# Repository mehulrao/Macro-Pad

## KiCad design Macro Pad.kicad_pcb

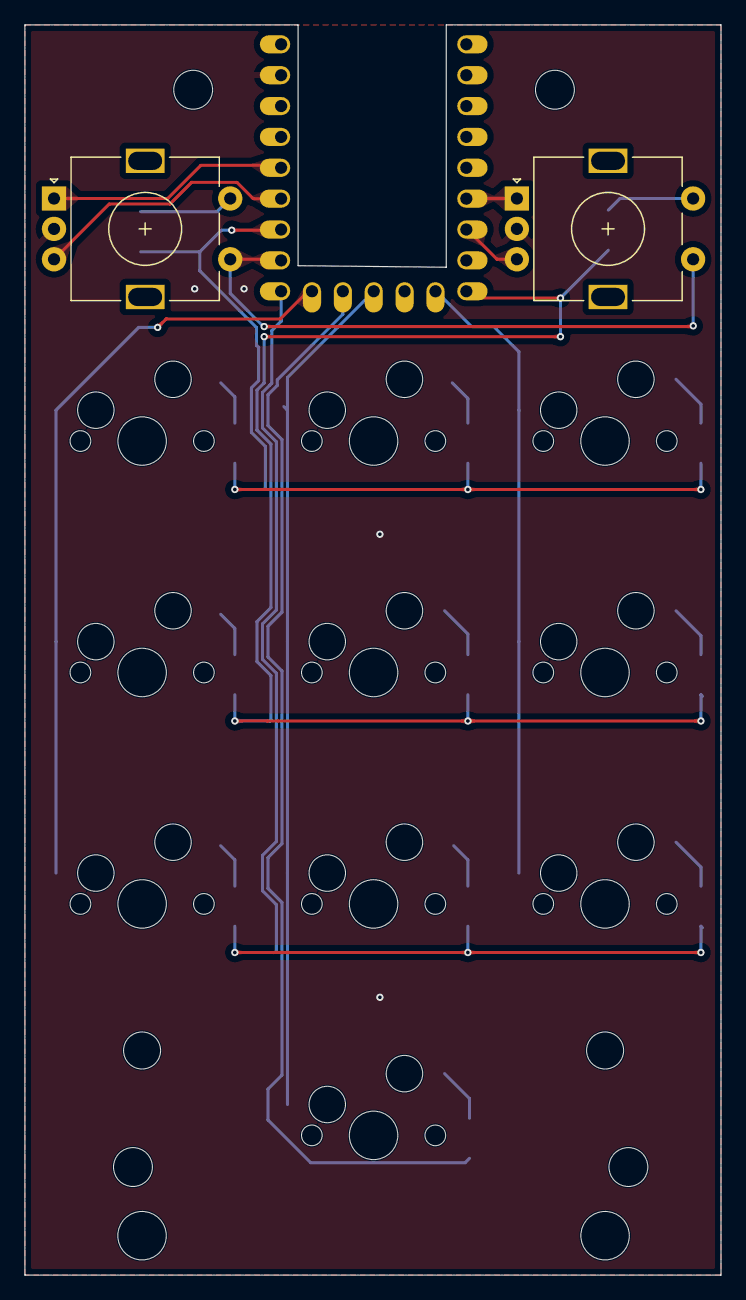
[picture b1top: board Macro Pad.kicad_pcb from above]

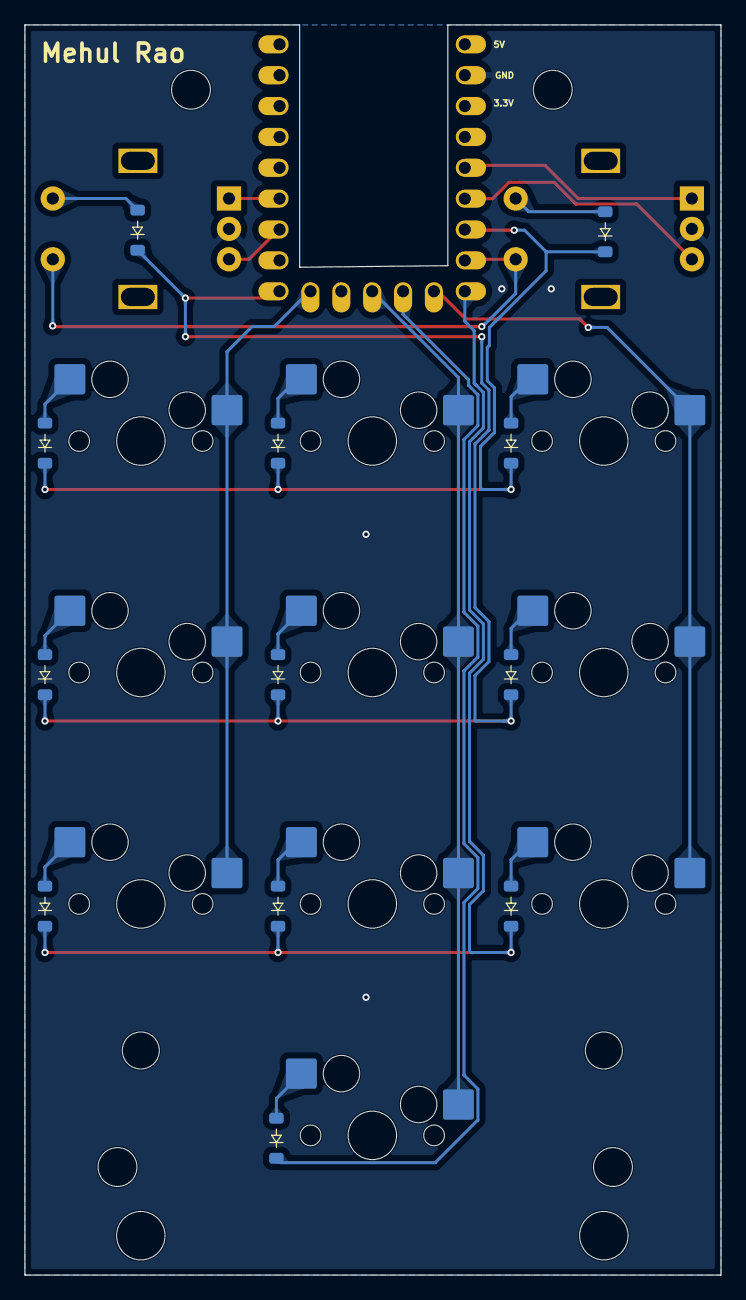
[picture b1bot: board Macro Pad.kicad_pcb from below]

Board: 2 copper layers, 57.3 x 102.9 mm, 29 parts (15 on the bottom side), 25 nets.

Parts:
D1, D2, D3, D4, D5, D6, D7, D8, D9, D10, D11, D12: D; MY_D_SOD-123
H1, H2, H3, H4: MountingHole; MountingHole_3.2mm_M3_ISO7380
K4, K5, K6, K8, K9, K10: KEYSW; MX-Hotswap-1U
SW1, SW2: RotaryEncoder_Switch; RotaryEncoder_Alps_EC11E-Switch_Vertical_H20mm
U1: rp2040-zero; rp2040-zero-tht
locked: KEYSW; MX-Hotswap-1U
locked#2, locked#3: KEYSW; MX-Hotswap-1U
locked#4: KEYSW; MX-Hotswap-3U

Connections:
/COL0: U1.14 (13), locked.1, locked#2.1, locked#3.1
/COL1: K4.1, K5.1, K6.1, U1.12 (11), locked#4.1
/COL2: K8.1, K9.1, K10.1, U1.10 (9)
/COL3: SW1.S1, SW2.S1, U1.16 (15)
/GND: SW1.C, SW2.C, U1.22 (GND)
/ROW0: D1.1 (K), D2.1 (K), D5.1 (K), D10.1 (K), U1.17 (26)
/ROW1: D3.1 (K), D4.1 (K), D6.1 (K), D11.1 (K), U1.9 (8)
/ROW2: D7.1 (K), D8.1 (K), D9.1 (K), U1.15 (14)
/ROW3: D12.1 (K), U1.13 (12)
/SW1_A: SW1.A, U1.19 (28)
/SW1_B: SW1.B, U1.18 (27)
/SW2_A: SW2.A, U1.6 (5)
/SW2_B: SW2.B, U1.7 (6)
unnamed: D1.2 (A), locked#2.2
unnamed: D2.2 (A), K4.2
unnamed: D3.2 (A), locked#3.2
unnamed: D4.2 (A), K5.2
unnamed: D5.2 (A), K8.2
unnamed: D6.2 (A), K9.2
unnamed: D7.2 (A), locked.2
unnamed: D8.2 (A), K6.2
unnamed: D9.2 (A), K10.2
unnamed: D10.2 (A), SW1.S2
unnamed: D11.2 (A), SW2.S2
unnamed: D12.2 (A), locked#4.2

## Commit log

2023-07-18 init
